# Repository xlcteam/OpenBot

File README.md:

This is a robot for the Robocup junior open competition created by Jakub Gál.
2020:
ISEF video:
https://www.youtube.com/watch?v=6aQB4FLPs9k

Robocup video:
https://vimeo.com/432606767

3D model:
https://grabcad.com/library/robocup-soccer-open-xlc-1

Dataset:
https://www.kaggle.com/jakubgal/robocup-junior-open-xlc

2021:
Video:
https://www.youtube.com/watch?v=bpfD3oBH6rc

TDP:
https://drive.google.com/drive/folders/1EIsMFVHUiWHSz9q-vNFF0SltVOlYTi-G?usp=sharing

XLC Team website:
https://xlc-team.info/

GrabCad:
https://grabcad.com/jakub.gal-2/models

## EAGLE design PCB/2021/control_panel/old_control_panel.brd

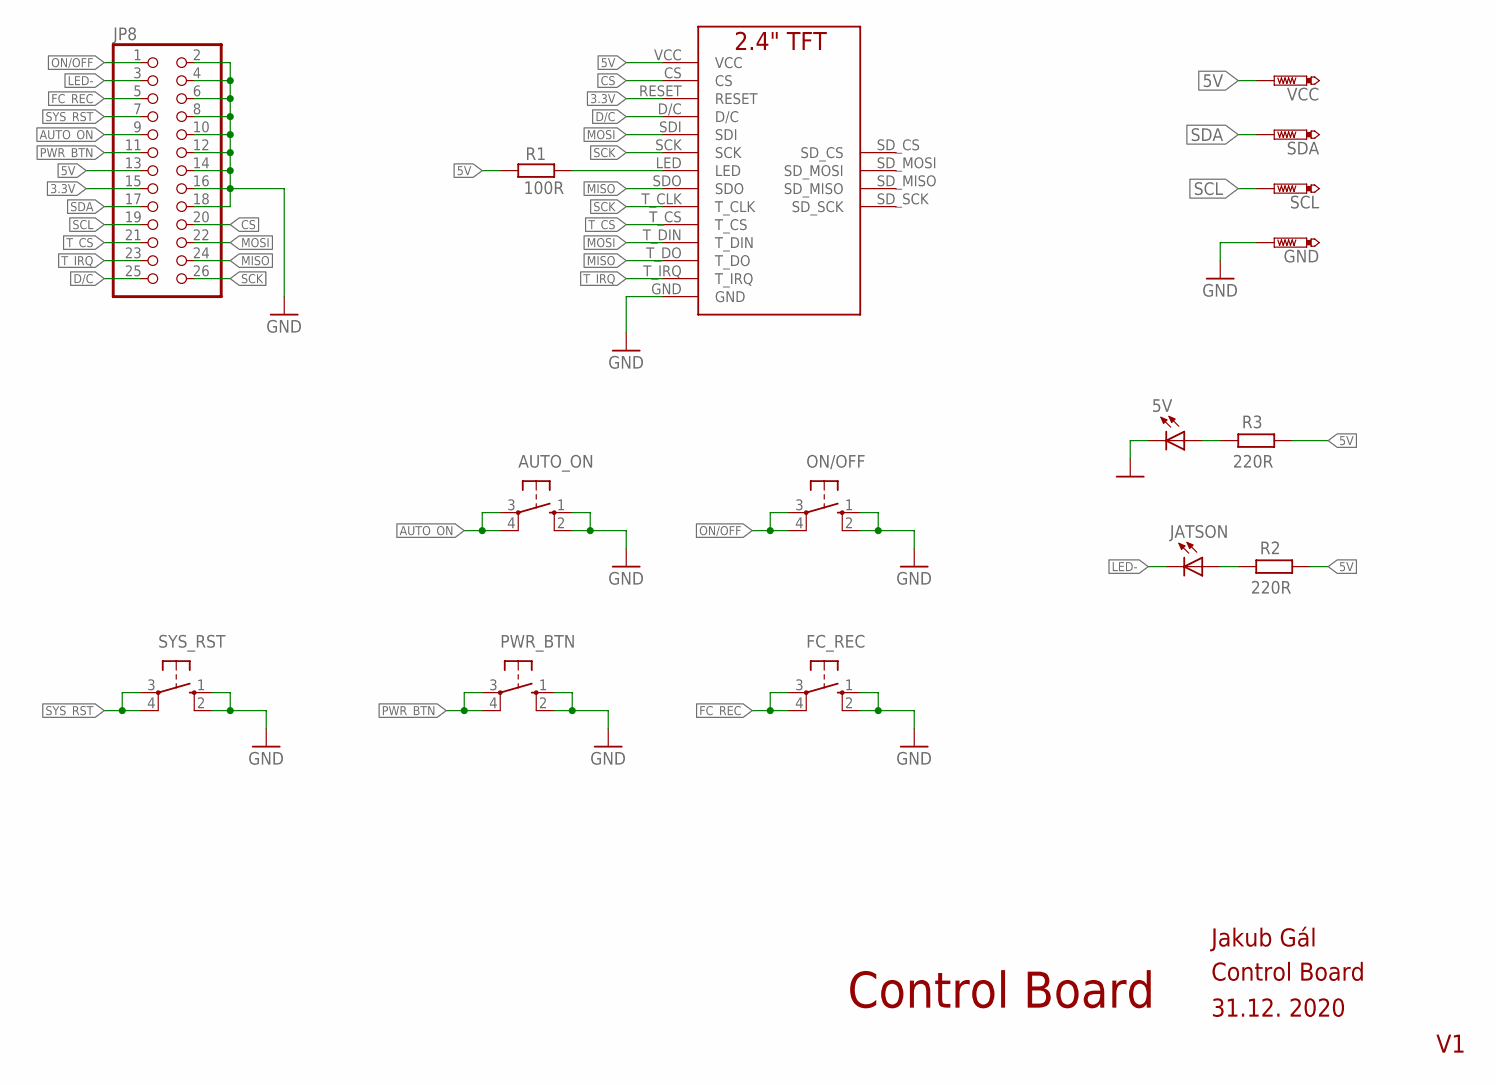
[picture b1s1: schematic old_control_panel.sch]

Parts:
5V: LEDCHIPLED_0603; CHIPLED_0603
AUTO_ON: 10-XX; B3F-10XX
FC_REC: 10-XX; B3F-10XX
GND: PTR1TP20R; TP20R
JATSON: LEDCHIPLED_0603; CHIPLED_0603
JP8: PINHD-2X13_2.54; 2X13
ON/OFF: 10-XX; B3F-10XX
PWR_BTN: 10-XX; B3F-10XX
R1: 100R; R0603
R2, R3: 220R; R0603
SCL: PTR1TP20R; TP20R
SDA: PTR1TP20R; TP20R
SYS_RST: 10-XX; B3F-10XX
U$1: 2.4"TFT; TFT_2.4"
VCC: PTR1TP20R; TP20R

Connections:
3.3V: JP8.15, U$1.RESET
5V: JP8.13, R1.1, R2.2, R3.2, U$1.VCC, VCC.TP
AUTO_ON: AUTO_ON.3, AUTO_ON.4 (P1), JP8.9
CS: JP8.20, U$1.CS
D/C: JP8.25, U$1.D/C
FC_REC: FC_REC.3, FC_REC.4 (P1), JP8.5
GND: 5V.C, AUTO_ON.1 (S), AUTO_ON.2 (S1), FC_REC.1 (S), FC_REC.2 (S1), GND.TP, JP8.2, JP8.4, JP8.6, JP8.8, JP8.10, JP8.12, JP8.14, JP8.16, JP8.18, ON/OFF.1 (S), ON/OFF.2 (S1), PWR_BTN.1 (S), PWR_BTN.2 (S1), SYS_RST.1 (S), SYS_RST.2 (S1), U$1.GND
LED-: JATSON.C, JP8.3
MISO: JP8.24, U$1.SDO, U$1.T_DO
MOSI: JP8.22, U$1.SDI, U$1.T_DIN
unnamed: R1.2, U$1.LED
unnamed: JATSON.A, R2.1
unnamed: 5V.A, R3.1
ON/OFF: JP8.1, ON/OFF.3, ON/OFF.4 (P1)
PWR_BTN: JP8.11, PWR_BTN.3, PWR_BTN.4 (P1)
SCK: JP8.26, U$1.SCK, U$1.T_CLK
SCL: JP8.19, SCL.TP
SDA: JP8.17, SDA.TP
SYS_RST: JP8.7, SYS_RST.3, SYS_RST.4 (P1)
T_CS: JP8.21, U$1.T_CS
T_IRQ: JP8.23, U$1.T_IRQ

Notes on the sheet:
Jakub Gál
Control Board
31.12. 2020

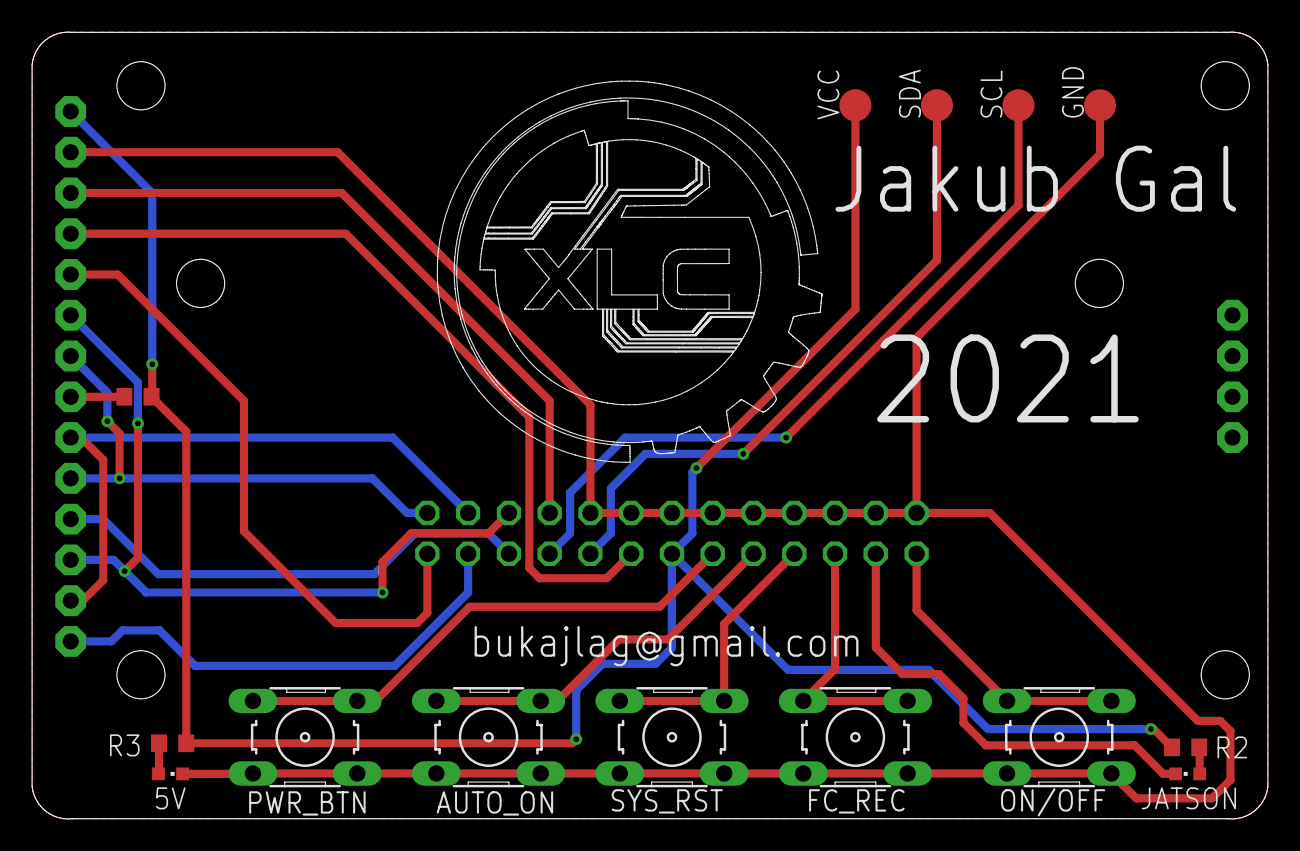
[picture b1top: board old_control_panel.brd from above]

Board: 2 copper layers, 77.0 x 49.0 mm, 16 parts (1 on the bottom side), 21 nets.

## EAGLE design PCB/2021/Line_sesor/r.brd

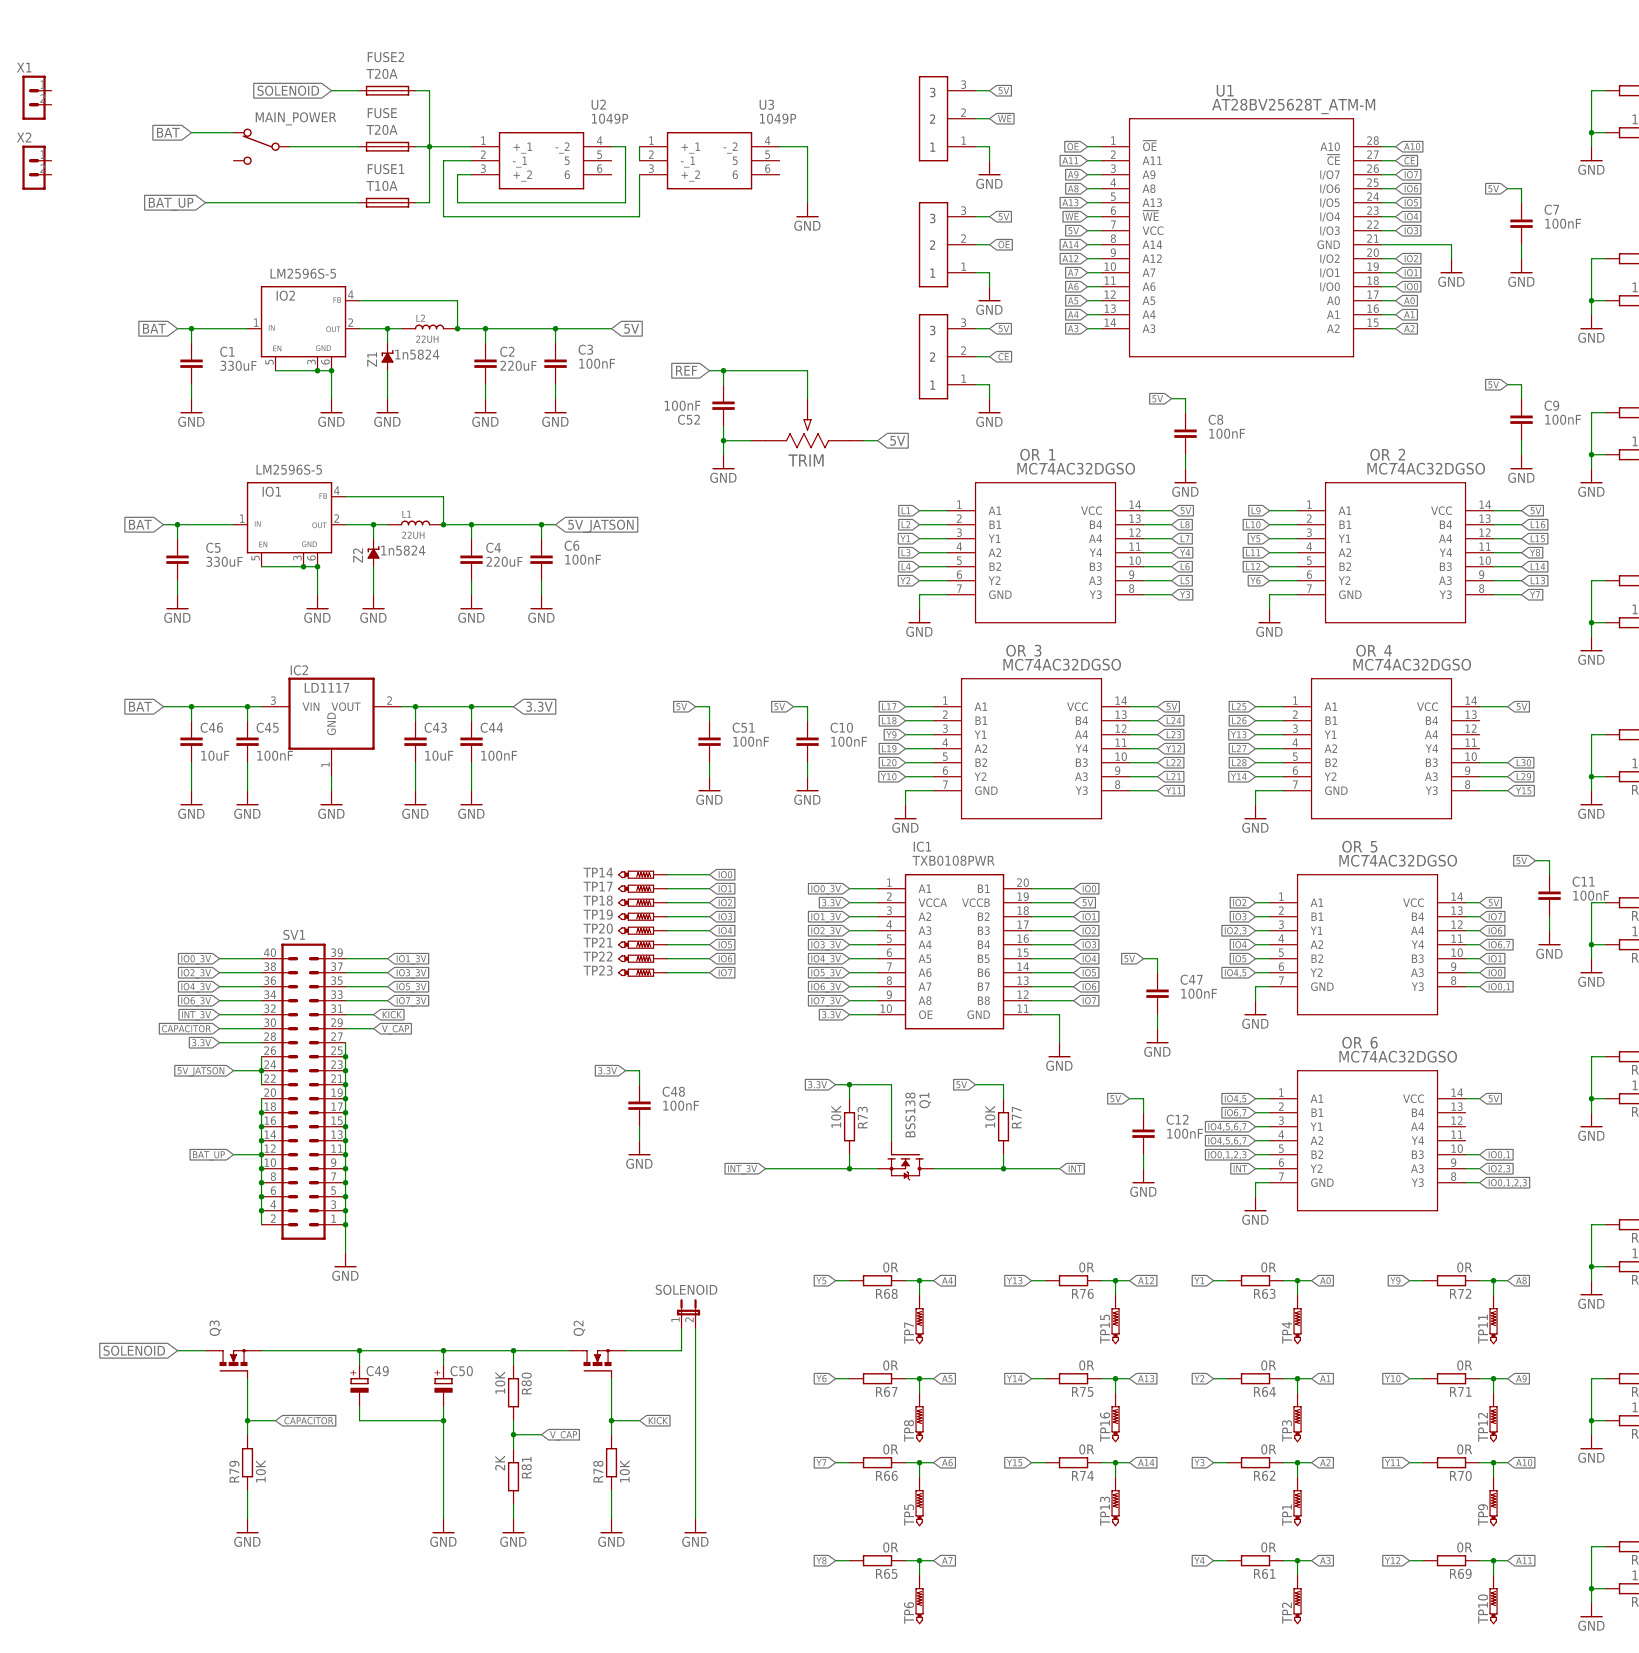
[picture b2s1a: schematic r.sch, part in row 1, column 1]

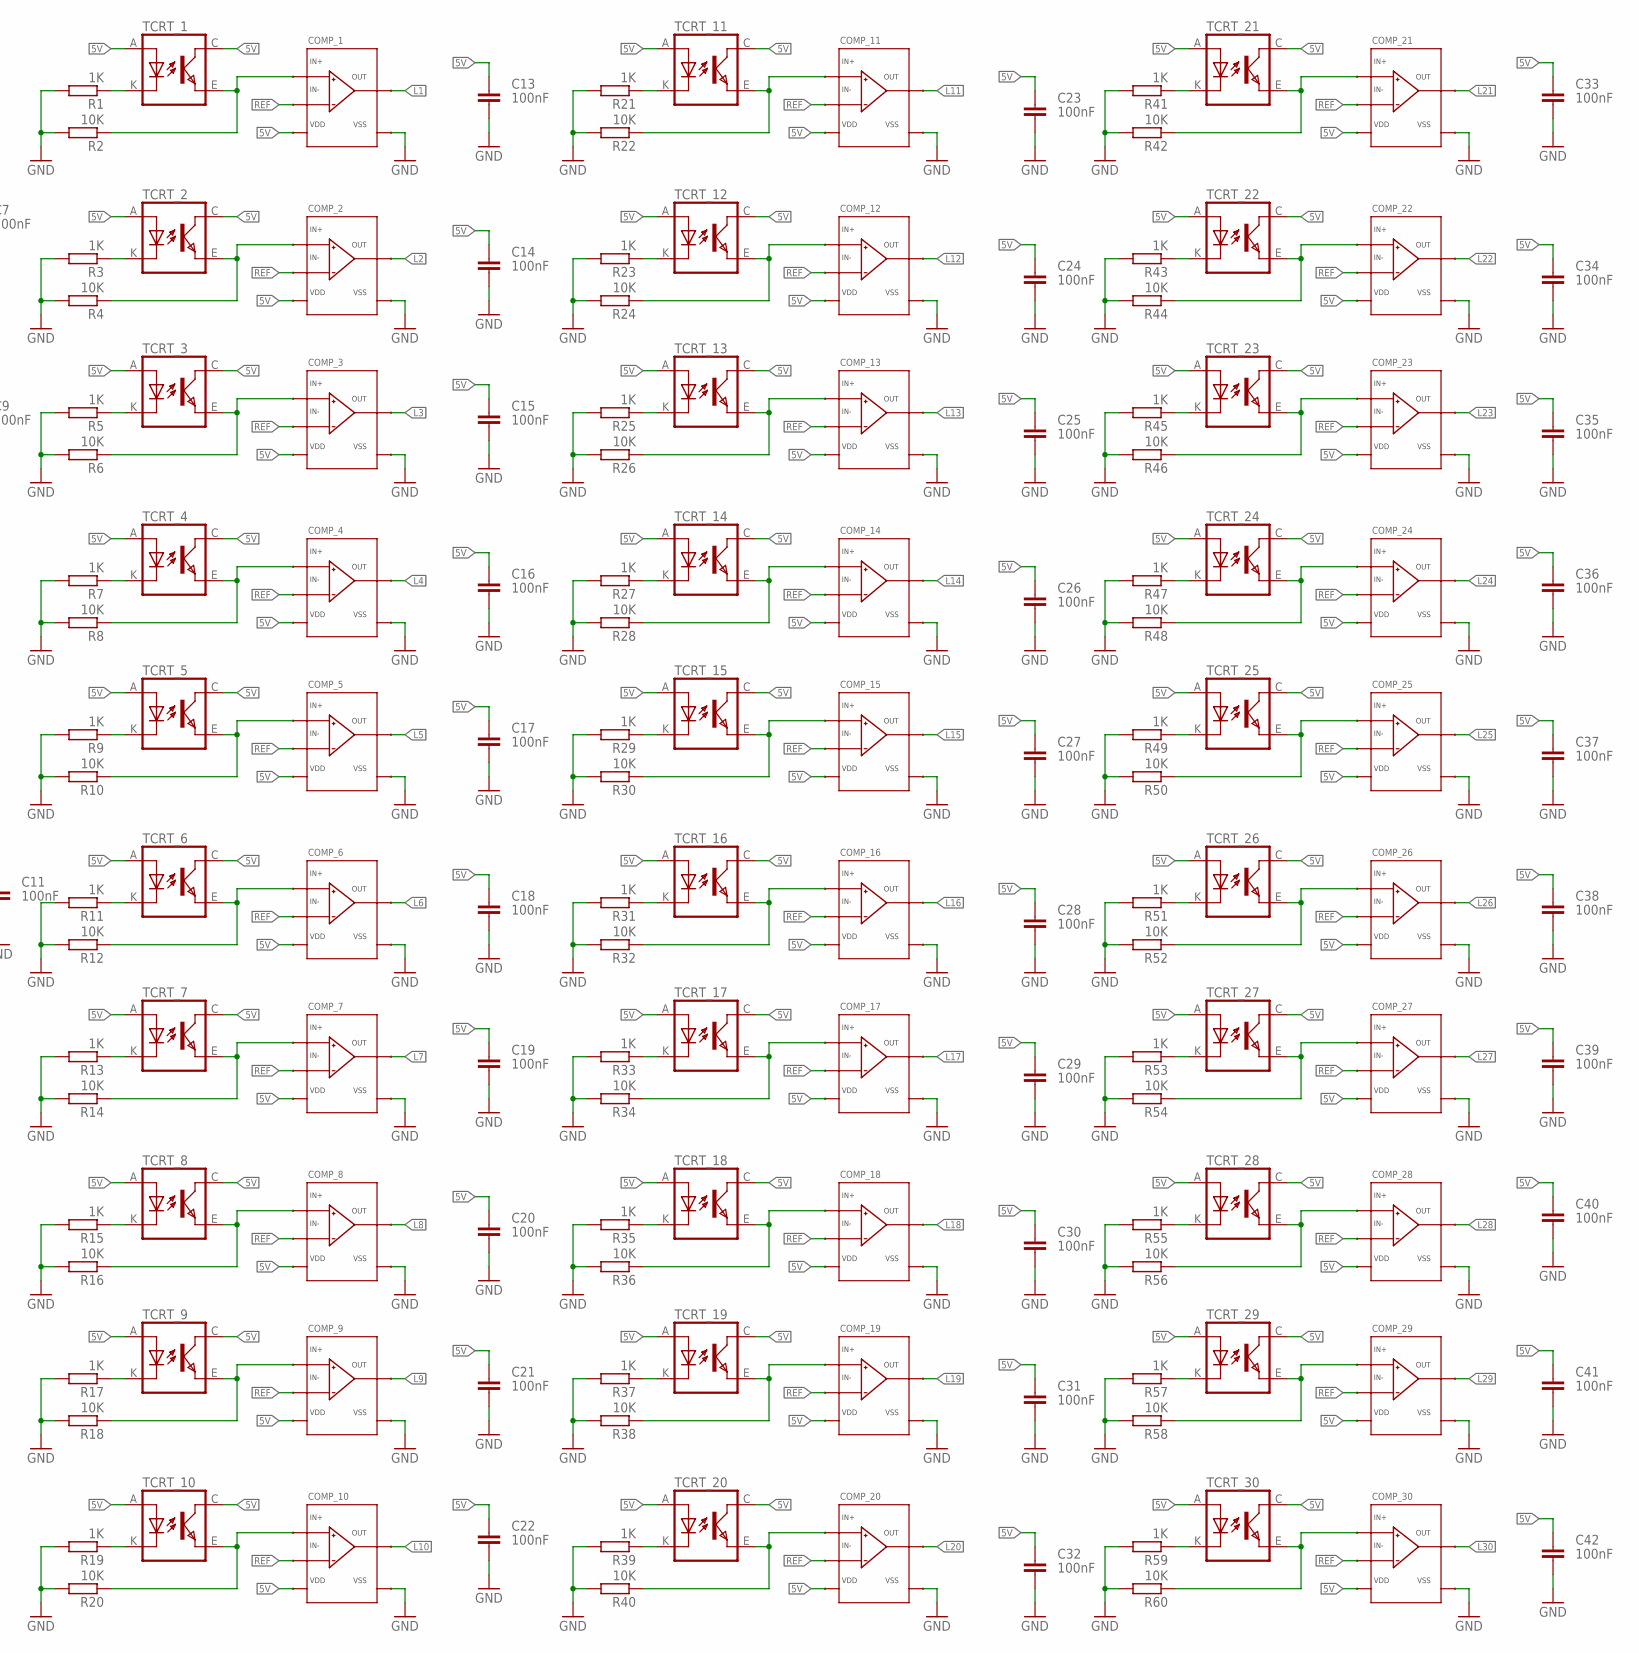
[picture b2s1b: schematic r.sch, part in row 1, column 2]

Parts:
C1, C5: 330uF; CAPM7343X310
C2, C4: 220uF; CAPM7343X310
C3, C6, C7, C8, C9, C10, C11, C12, C13, C14, C15, C16, C17, C18, C19, C20, C21, C22, C23, C24, C25, C26, C27, C28, C29, C30, C31, C32, C33, C34, C35, C36, C37, C38, C39, C40, C41, C42, C44, C45, C47, C48, C51, C52: 100nF; C0603
C43, C46: 10uF; C0603
C49, C50: CPOL-EUE10-30; EB30D
COMP_1, COMP_2, COMP_3, COMP_4, COMP_5, COMP_6, COMP_7, COMP_8, COMP_9, COMP_10, COMP_11, COMP_12, COMP_13, COMP_14, COMP_15, COMP_16, COMP_17, COMP_18, COMP_19, COMP_20, COMP_21, COMP_22, COMP_23, COMP_24, COMP_25, COMP_26, COMP_27, COMP_28, COMP_29, COMP_30: TC75S56FUTE85LF; SOT-353___(USV)_TOS
FUSE, FUSE2: T20A; SH22,5A
FUSE1: T10A; SH22,5A
IC1: TXB0108PWR; SOP65P640X120-20N
IC2: LD1117; SOT223
IO1, IO2: LM2596S-5; TO263-5
L1, L2: 22UH; INDUCTOR_L0630
MAIN_POWER: PREP-1PB; P-B069B
OR_1, OR_2, OR_3, OR_4, OR_5, OR_6: MC74AC32DGSO; SOIC-14_NB_ONS-M
Q1: BSS138; SOT23
Q2, Q3: PMOSFET_NTO220BV; TO220BV
R1, R3, R5, R7, R9, R11, R13, R15, R17, R19, R21, R23, R25, R27, R29, R31, R33, R35, R37, R39, R41, R43, R45, R47, R49, R51, R53, R55, R57, R59: 1K; R0603
R2, R4, R6, R8, R10, R12, R14, R16, R18, R20, R22, R24, R26, R28, R30, R32, R34, R36, R38, R40, R42, R44, R46, R48, R50, R52, R54, R56, R58, R60, R73, R77, R80: 10K; R0603
R61, R62, R63, R64, R65, R66, R67, R68, R69, R70, R71, R72, R74, R75, R76: 0R; R0603
R78, R79: 10K; R1206
R81: 2K; R0603
SOLENOID: JP1E; JP1
SV1: MLW40; ML40
TCRT_1, TCRT_2, TCRT_3, TCRT_4, TCRT_5, TCRT_6, TCRT_7, TCRT_8, TCRT_9, TCRT_10, TCRT_11, TCRT_12, TCRT_13, TCRT_14, TCRT_15, TCRT_16, TCRT_17, TCRT_18, TCRT_19, TCRT_20, TCRT_21, TCRT_22, TCRT_23, TCRT_24, TCRT_25, TCRT_26, TCRT_27, TCRT_28, TCRT_29, TCRT_30: TCRT5000
TP1, TP2, TP3, TP4, TP5, TP6, TP7, TP8, TP9, TP10, TP11, TP12, TP13, TP14, TP15, TP16, TP17, TP18, TP19, TP20, TP21, TP22, TP23: PTR1TP20R; TP20R
TRIM: 3362W-1-103LF; POT_3362W
U1: AT28BV25628T_ATM-M; 28T_ATM-M
U2, U3: 1049P
U$1, U$2, U$3: 0603_S
X1, X2: ML2"; ML2
Z1, Z2: 1n5824; SUPRESSOR_SMAJ

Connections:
3.3V: C43.1, C44.1, C48.1, IC1.2 (VCCA), IC1.10 (OE), IC2.2 (VOUT), Q1.1 (G), R73.1, SV1.28
5V: C2.1, C3.1, C7.1, C8.1, C9.1, C10.1, C11.1, C12.1, C13.1, C14.1, C15.1, C16.1, C17.1, C18.1, C19.1, C20.1, C21.1, C22.1, C23.1, C24.1, C25.1, C26.1, C27.1, C28.1, C29.1, C30.1, C31.1, C32.1, C33.1, C34.1, C35.1, C36.1, C37.1, C38.1, C39.1, C40.1, C41.1, C42.1, C47.1, C51.1, COMP_1.5, COMP_2.5, COMP_3.5, COMP_4.5, COMP_5.5, COMP_6.5, COMP_7.5, COMP_8.5, COMP_9.5, COMP_10.5, COMP_11.5, COMP_12.5, COMP_13.5, COMP_14.5, COMP_15.5, COMP_16.5, COMP_17.5, COMP_18.5, COMP_19.5, COMP_20.5, COMP_21.5, COMP_22.5, COMP_23.5, COMP_24.5, COMP_25.5, COMP_26.5, COMP_27.5, COMP_28.5, COMP_29.5, COMP_30.5, IC1.19 (VCCB), IO2.4 (FB), L2.2, OR_1.14 (VCC), OR_2.14 (VCC), OR_3.14 (VCC), OR_4.14 (VCC), OR_5.14 (VCC), OR_6.14 (VCC), R77.1, TCRT_1.A (ANODE), TCRT_1.C (COLLECTOR), TCRT_2.A (ANODE), TCRT_2.C (COLLECTOR), TCRT_3.A (ANODE), TCRT_3.C (COLLECTOR), TCRT_4.A (ANODE), TCRT_4.C (COLLECTOR), TCRT_5.A (ANODE), TCRT_5.C (COLLECTOR), TCRT_6.A (ANODE), TCRT_6.C (COLLECTOR), TCRT_7.A (ANODE), TCRT_7.C (COLLECTOR), TCRT_8.A (ANODE), TCRT_8.C (COLLECTOR), TCRT_9.A (ANODE), TCRT_9.C (COLLECTOR), TCRT_10.A (ANODE), TCRT_10.C (COLLECTOR), TCRT_11.A (ANODE), TCRT_11.C (COLLECTOR), TCRT_12.A (ANODE), TCRT_12.C (COLLECTOR), TCRT_13.A (ANODE), TCRT_13.C (COLLECTOR), TCRT_14.A (ANODE), TCRT_14.C (COLLECTOR), TCRT_15.A (ANODE), TCRT_15.C (COLLECTOR), TCRT_16.A (ANODE), TCRT_16.C (COLLECTOR), TCRT_17.A (ANODE), TCRT_17.C (COLLECTOR), TCRT_18.A (ANODE), TCRT_18.C (COLLECTOR), TCRT_19.A (ANODE), TCRT_19.C (COLLECTOR), TCRT_20.A (ANODE), TCRT_20.C (COLLECTOR), TCRT_21.A (ANODE), TCRT_21.C (COLLECTOR), TCRT_22.A (ANODE), TCRT_22.C (COLLECTOR), TCRT_23.A (ANODE), TCRT_23.C (COLLECTOR), TCRT_24.A (ANODE), TCRT_24.C (COLLECTOR), TCRT_25.A (ANODE), TCRT_25.C (COLLECTOR), TCRT_26.A (ANODE), TCRT_26.C (COLLECTOR), TCRT_27.A (ANODE), TCRT_27.C (COLLECTOR), TCRT_28.A (ANODE), TCRT_28.C (COLLECTOR), TCRT_29.A (ANODE), TCRT_29.C (COLLECTOR), TCRT_30.A (ANODE)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
5V_JATSON: C4.1, C6.1, IO1.4 (FB), L1.2, SV1.22, SV1.24, SV1.26
!CE: U1.27 (!CE), U$3.2 (A2)
!OE: U1.1 (!OE), U$2.2 (A2)
!WE: U1.6 (!WE), U$1.2 (A2)
A0: R63.1, TP4.TP, U1.17 (A0)
A1: R64.1, TP3.TP, U1.16 (A1)
A2: R62.1, TP1.TP, U1.15 (A2)
A3: R61.1, TP2.TP, U1.14 (A3)
A4: R68.1, TP7.TP, U1.13 (A4)
A5: R67.1, TP8.TP, U1.12 (A5)
A6: R66.1, TP5.TP, U1.11 (A6)
A7: R65.1, TP6.TP, U1.10 (A7)
A8: R72.1, TP11.TP, U1.4 (A8)
A9: R71.1, TP12.TP, U1.3 (A9)
A10: R70.1, TP9.TP, U1.28 (A10)
A11: R69.1, TP10.TP, U1.2 (A11)
A12: R76.1, TP15.TP, U1.9 (A12)
A13: R75.1, TP16.TP, U1.5 (A13)
A14: R74.1, TP13.TP, U1.8 (A14)
BAT: C1.1, C5.1, C45.1, C46.1, IC2.3 (VIN), IO1.1 (IN), IO2.1 (IN), MAIN_POWER.3 (3-ON)
BAT_UP: FUSE1.1, SV1.2, SV1.4, SV1.6, SV1.8, SV1.10, SV1.12, SV1.14, SV1.16, SV1.18, SV1.20
CAPACITOR: Q3.G, R79.2, SV1.30
GND: C1.2, C2.2, C3.2, C4.2, C5.2, C6.2, C7.2, C8.2, C9.2, C10.2, C11.2, C12.2, C13.2, C14.2, C15.2, C16.2, C17.2, C18.2, C19.2, C20.2, C21.2, C22.2, C23.2, C24.2, C25.2, C26.2, C27.2, C28.2, C29.2, C30.2, C31.2, C32.2, C33.2, C34.2, C35.2, C36.2, C37.2, C38.2, C39.2, C40.2, C41.2, C42.2, C43.2, C44.2, C45.2, C46.2, C47.2, C48.2, C49.-, C50.-, C51.2, C52.1, COMP_1.2, COMP_2.2, COMP_3.2, COMP_4.2, COMP_5.2, COMP_6.2, COMP_7.2, COMP_8.2, COMP_9.2, COMP_10.2, COMP_11.2, COMP_12.2, COMP_13.2, COMP_14.2, COMP_15.2, COMP_16.2, COMP_17.2, COMP_18.2, COMP_19.2, COMP_20.2, COMP_21.2, COMP_22.2, COMP_23.2, COMP_24.2, COMP_25.2, COMP_26.2, COMP_27.2, COMP_28.2, COMP_29.2, COMP_30.2, IC1.11 (GND), IC2.1 (GND), IO1.3 (GND), IO1.5 (EN), IO1.6 (GND), IO2.3 (GND), IO2.5 (EN), IO2.6 (GND), OR_1.7 (GND), OR_2.7 (GND), OR_3.7 (GND), OR_4.7 (GND), OR_5.7 (GND), OR_6.7 (GND), R1.2, R2.2, R3.2, R4.2, R5.2, R6.2, R7.2, R8.2, R9.2, R10.2, R11.2, R12.2, R13.2, R14.2, R15.2, R16.2, R17.2, R18.2, R19.2, R20.2, R21.2, R22.2, R23.2, R24.2, R25.2, R26.2, R27.2, R28.2, R29.2, R30.2, R31.2, R32.2, R33.2, R34.2, R35.2, R36.2, R37.2, R38.2, R39.2, R40.2, R41.2, R42.2, R43.2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
INT: OR_6.6 (Y2), Q1.3 (D), R77.2
INT_3V: Q1.2 (S), R73.2, SV1.32
IO0: IC1.20 (B1), OR_5.9 (A3), TP14.TP, U1.18 (I/O0)
IO0,1: OR_5.8 (Y3), OR_6.10 (B3)
IO0,1,2,3: OR_6.5 (B2), OR_6.8 (Y3)
IO0_3V: IC1.1 (A1), SV1.40
IO1: IC1.18 (B2), OR_5.10 (B3), TP17.TP, U1.19 (I/O1)
IO1_3V: IC1.3 (A2), SV1.39
IO2: IC1.17 (B3), OR_5.1 (A1), TP18.TP, U1.20 (I/O2)
IO2,3: OR_5.3 (Y1), OR_6.9 (A3)
IO2_3V: IC1.4 (A3), SV1.38
IO3: IC1.16 (B4), OR_5.2 (B1), TP19.TP, U1.22 (I/O3)
IO3_3V: IC1.5 (A4), SV1.37
IO4: IC1.15 (B5), OR_5.4 (A2), TP20.TP, U1.23 (I/O4)
IO4,5: OR_5.6 (Y2), OR_6.1 (A1)
IO4,5,6,7: OR_6.3 (Y1), OR_6.4 (A2)
IO4_3V: IC1.6 (A5), SV1.36
IO5: IC1.14 (B6), OR_5.5 (B2), TP21.TP, U1.24 (I/O5)
IO5_3V: IC1.7 (A6), SV1.35
IO6: IC1.13 (B7), OR_5.12 (A4), TP22.TP, U1.25 (I/O6)
IO6,7: OR_5.11 (Y4), OR_6.2 (B1)
IO6_3V: IC1.8 (A7), SV1.34
IO7: IC1.12 (B8), OR_5.13 (B4), TP23.TP, U1.26 (I/O7)
IO7_3V: IC1.9 (A8), SV1.33
KICK: Q2.G, R78.2, SV1.31
L1: COMP_1.4, OR_1.1 (A1)
L2: COMP_2.4, OR_1.2 (B1)
L3: COMP_3.4, OR_1.4 (A2)
L4: COMP_4.4, OR_1.5 (B2)
L5: COMP_5.4, OR_1.9 (A3)
L6: COMP_6.4, OR_1.10 (B3)
L7: COMP_7.4, OR_1.12 (A4)
L8: COMP_8.4, OR_1.13 (B4)
L9: COMP_9.4, OR_2.1 (A1)
L10: COMP_10.4, OR_2.2 (B1)
L11: COMP_11.4, OR_2.4 (A2)
L12: COMP_12.4, OR_2.5 (B2)
L13: COMP_13.4, OR_2.9 (A3)
L14: COMP_14.4, OR_2.10 (B3)
L15: COMP_15.4, OR_2.12 (A4)
L16: COMP_16.4, OR_2.13 (B4)
L17: COMP_17.4, OR_3.1 (A1)
L18: COMP_18.4, OR_3.2 (B1)
L19: COMP_19.4, OR_3.4 (A2)
L20: COMP_20.4, OR_3.5 (B2)
L21: COMP_21.4, OR_3.9 (A3)
L22: COMP_22.4, OR_3.10 (B3)
L23: COMP_23.4, OR_3.12 (A4)
L24: COMP_24.4, OR_3.13 (B4)
L25: COMP_25.4, OR_4.1 (A1)
L26: COMP_26.4, OR_4.2 (B1)
L27: COMP_27.4, OR_4.4 (A2)
L28: COMP_28.4, OR_4.5 (B2)
L29: COMP_29.4, OR_4.9 (A3)
L30: COMP_30.4, OR_4.10 (B3)
unnamed: R1.1, TCRT_1.K (CATHODE)
unnamed: COMP_1.3, R2.1, TCRT_1.E (EMITTER)
unnamed: R3.1, TCRT_2.K (CATHODE)
unnamed: COMP_2.3, R4.1, TCRT_2.E (EMITTER)
unnamed: R5.1, TCRT_3.K (CATHODE)
unnamed: COMP_3.3, R6.1, TCRT_3.E (EMITTER)
unnamed: R7.1, TCRT_4.K (CATHODE)
unnamed: COMP_4.3, R8.1, TCRT_4.E (EMITTER)
unnamed: R9.1, TCRT_5.K (CATHODE)
unnamed: COMP_5.3, R10.1, TCRT_5.E (EMITTER)
unnamed: R11.1, TCRT_6.K (CATHODE)
unnamed: COMP_6.3, R12.1, TCRT_6.E (EMITTER)
unnamed: R13.1, TCRT_7.K (CATHODE)
unnamed: COMP_7.3, R14.1, TCRT_7.E (EMITTER)
unnamed: R15.1, TCRT_8.K (CATHODE)
unnamed: COMP_8.3, R16.1, TCRT_8.E (EMITTER)
unnamed: R17.1, TCRT_9.K (CATHODE)
unnamed: COMP_9.3, R18.1, TCRT_9.E (EMITTER)
unnamed: R19.1, TCRT_10.K (CATHODE)
unnamed: COMP_10.3, R20.1, TCRT_10.E (EMITTER)
unnamed: R21.1, TCRT_11.K (CATHODE)
unnamed: COMP_11.3, R22.1, TCRT_11.E (EMITTER)
unnamed: R23.1, TCRT_12.K (CATHODE)
unnamed: COMP_12.3, R24.1, TCRT_12.E (EMITTER)
unnamed: R25.1, TCRT_13.K (CATHODE)
unnamed: COMP_13.3, R26.1, TCRT_13.E (EMITTER)
unnamed: R27.1, TCRT_14.K (CATHODE)
unnamed: COMP_14.3, R28.1, TCRT_14.E (EMITTER)
unnamed: R29.1, TCRT_15.K (CATHODE)
unnamed: COMP_15.3, R30.1, TCRT_15.E (EMITTER)
unnamed: R31.1, TCRT_16.K (CATHODE)
unnamed: COMP_16.3, R32.1, TCRT_16.E (EMITTER)
unnamed: R33.1, TCRT_17.K (CATHODE)
unnamed: COMP_17.3, R34.1, TCRT_17.E (EMITTER)
unnamed: R35.1, TCRT_18.K (CATHODE)
unnamed: COMP_18.3, R36.1, TCRT_18.E (EMITTER)
unnamed: R37.1, TCRT_19.K (CATHODE)
unnamed: COMP_19.3, R38.1, TCRT_19.E (EMITTER)
unnamed: R39.1, TCRT_20.K (CATHODE)
unnamed: COMP_20.3, R40.1, TCRT_20.E (EMITTER)
unnamed: R41.1, TCRT_21.K (CATHODE)
unnamed: COMP_21.3, R42.1, TCRT_21.E (EMITTER)
unnamed: R43.1, TCRT_22.K (CATHODE)
unnamed: COMP_22.3, R44.1, TCRT_22.E (EMITTER)
unnamed: R45.1, TCRT_23.K (CATHODE)
unnamed: COMP_23.3, R46.1, TCRT_23.E (EMITTER)
unnamed: R47.1, TCRT_24.K (CATHODE)
unnamed: COMP_24.3, R48.1, TCRT_24.E (EMITTER)
unnamed: R49.1, TCRT_25.K (CATHODE)
unnamed: COMP_25.3, R50.1, TCRT_25.E (EMITTER)
unnamed: R51.1, TCRT_26.K (CATHODE)
unnamed: COMP_26.3, R52.1, TCRT_26.E (EMITTER)
unnamed: R53.1, TCRT_27.K (CATHODE)
unnamed: COMP_27.3, R54.1, TCRT_27.E (EMITTER)
unnamed: R55.1, TCRT_28.K (CATHODE)
unnamed: COMP_28.3, R56.1, TCRT_28.E (EMITTER)
unnamed: R57.1, TCRT_29.K (CATHODE)
unnamed: COMP_29.3, R58.1, TCRT_29.E (EMITTER)
unnamed: R59.1, TCRT_30.K (CATHODE)
unnamed: COMP_30.3, R60.1, TCRT_30.E (EMITTER)
unnamed: IO2.2 (OUT), L2.1, Z1.C
unnamed: IO1.2 (OUT), L1.1, Z2.C
unnamed: U2.3 (+_2), U2.4 (-_2)
unnamed: U3.1 (+_1), U3.2 (-_1)
unnamed: U2.2 (-_1), U3.3 (+_2)
unnamed: FUSE.2, FUSE1.2, FUSE2.2, U2.1 (+_1)
unnamed: FUSE.1, MAIN_POWER.2 (2-COM)
unnamed: C49.+, C50.+, Q2.D, Q3.S, R80.1
unnamed: Q2.S, SOLENOID.1
REF: C52.2, COMP_1.1, COMP_2.1, COMP_3.1, COMP_4.1, COMP_5.1, COMP_6.1, COMP_7.1, COMP_8.1, COMP_9.1, COMP_10.1, COMP_11.1, COMP_12.1, COMP_13.1, COMP_14.1, COMP_15.1, COMP_16.1, COMP_17.1, COMP_18.1, COMP_19.1, COMP_20.1, COMP_21.1, COMP_22.1, COMP_23.1, COMP_24.1, COMP_25.1, COMP_26.1, COMP_27.1, COMP_28.1, COMP_29.1, COMP_30.1, TRIM.2
SOLENOID: FUSE2.1, Q3.D
V_CAP: R80.2, R81.1, SV1.29
Y1: OR_1.3 (Y1), R63.2
Y2: OR_1.6 (Y2), R64.2
Y3: OR_1.8 (Y3), R62.2
Y4: OR_1.11 (Y4), R61.2
Y5: OR_2.3 (Y1), R68.2
Y6: OR_2.6 (Y2), R67.2
Y7: OR_2.8 (Y3), R66.2
Y8: OR_2.11 (Y4), R65.2
Y9: OR_3.3 (Y1), R72.2
Y10: OR_3.6 (Y2), R71.2
Y11: OR_3.8 (Y3), R70.2
Y12: OR_3.11 (Y4), R69.2
Y13: OR_4.3 (Y1), R76.2
Y14: OR_4.6 (Y2), R75.2
Y15: OR_4.8 (Y3), R74.2

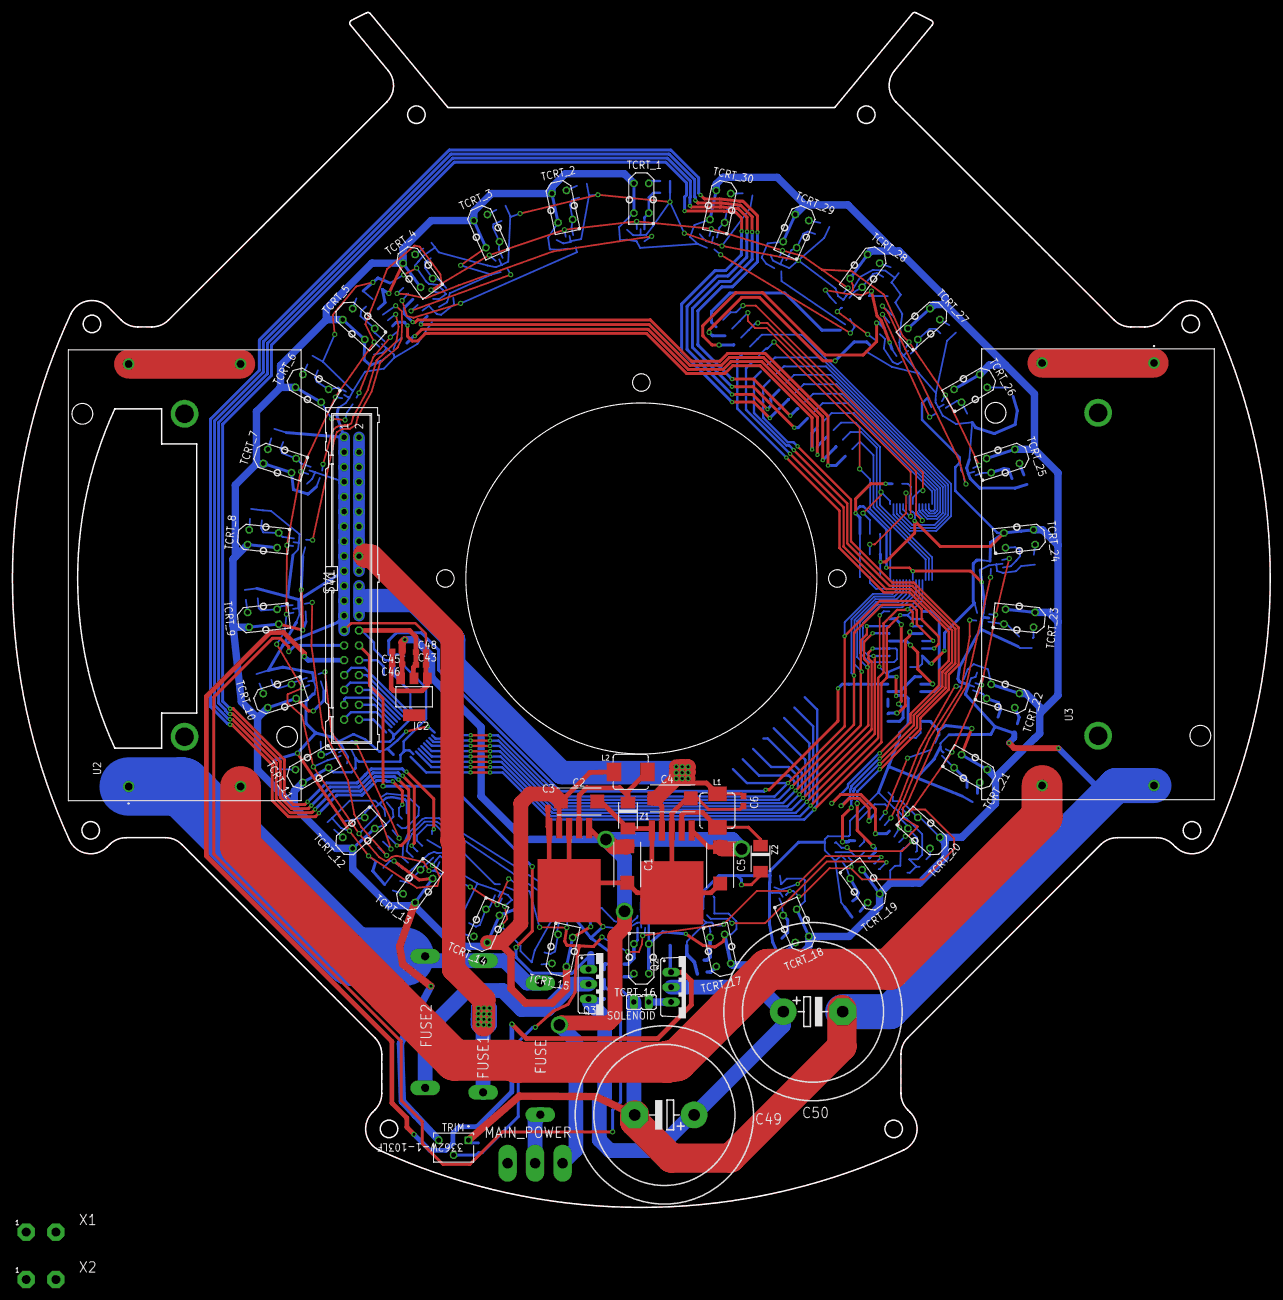
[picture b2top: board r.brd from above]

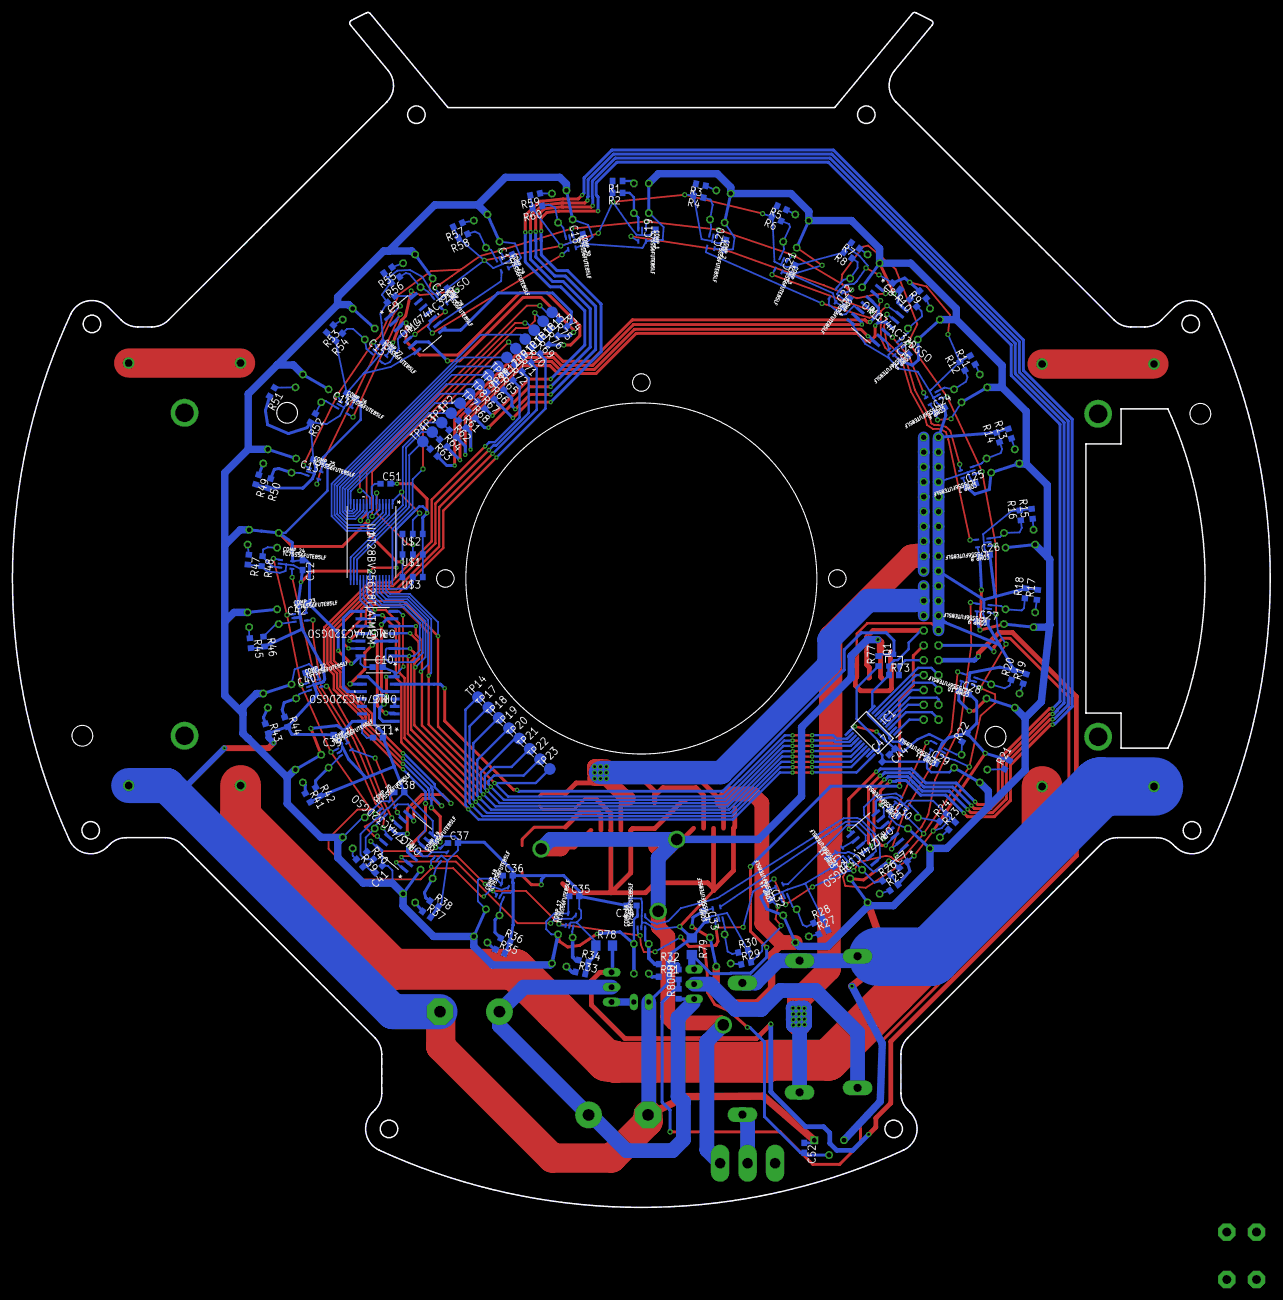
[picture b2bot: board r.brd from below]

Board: 2 copper layers, 215.0 x 204.3 mm, 248 parts (186 on the bottom side), 167 nets.

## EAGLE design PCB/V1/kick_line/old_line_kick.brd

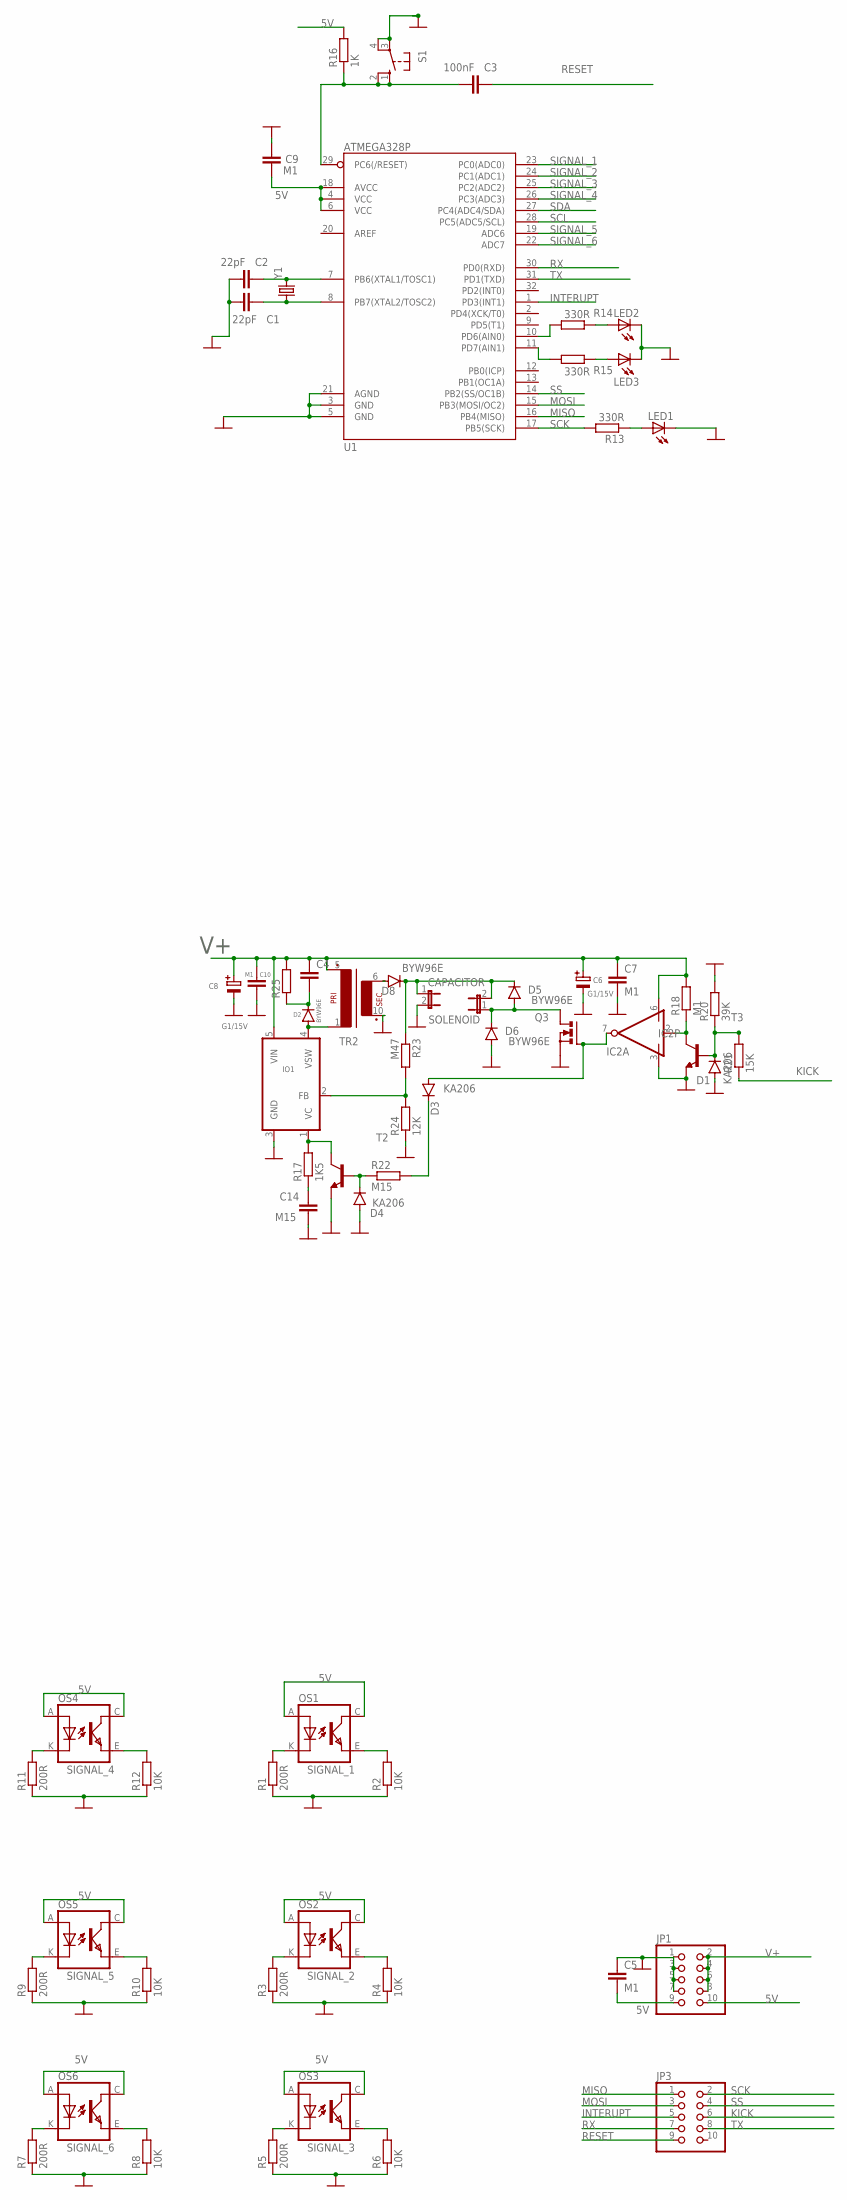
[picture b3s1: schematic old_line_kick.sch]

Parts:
C1, C2: 22pF; C0603
C3: 100nF; C0603
C4: C-EU075-052X106; C075-052X106
C5, C9: M1; C0603
C6, C8: G1/15V; E-2,5/7-RAD
C7, C10: M1; C0805K
C14: M15; C1206
CAPACITOR: JP1E; JP1
D1, D3, D4: KA206; D-7.5
D2, D5, D6, D8: BYW96E; SOD64-10
IC2: MIC4423BM; SO08
IO1: LT1071V; TO220-5P
JP1, JP3: PINHD-2X5IDC; 2X05_IDC
LED1, LED2, LED3: LEDCHIPLED_0603; CHIPLED_0603
OS1, OS2, OS3, OS4, OS5, OS6: TCRT5000
Q3: PMOSFET_NTO220BV; TO220BV
R1, R3, R5, R7, R9, R11: 200R; R0603
R2, R4, R6, R8, R10, R12: 10K; R0603
R13, R14, R15: 330R; R0603
R16: 1K; R0603
R17: 1K5; R1206
R18: M1; R1206
R20: 39K; R1206
R21: 15K; R1206
R22: M15; R1206
R23: M47; R1206
R24: 12K; R1206
R25: REZISTOR-7,5MM-HORIZ; R-7,5H
S1: 10-XX; B3F-10XX
SOLENOID: JP1E; JP1
T2, T3: -NPN-SC59-BEC; SC59-BEC
TR2: TRAFO-E10-R""; TRAFO-EE17X20
U1: ATMEGA328P; TQFP32-08
Y1: CRYSTALHC49US; HC49US

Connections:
5V: C5.2, C9.1, JP1.9, JP1.10, OS1.A (ANODE), OS1.C (COLLECTOR), OS2.A (ANODE), OS2.C (COLLECTOR), OS3.A (ANODE), OS3.C (COLLECTOR), OS4.A (ANODE), OS4.C (COLLECTOR), OS5.A (ANODE), OS5.C (COLLECTOR), OS6.A (ANODE), OS6.C (COLLECTOR), R16.2, U1.4 (VCC), U1.6 (VCC), U1.18 (AVCC)
GND: C1.1, C2.1, C5.1, C6.-, C7.2, C8.-, C9.2, C10.2, C14.2, CAPACITOR.2, D1.A, D4.A, D6.A, IC2.3 (GND), IO1.3 (GND), JP1.1, JP1.3, JP1.5, JP1.7, LED1.C, LED2.C, LED3.C, Q3.S, R1.1, R2.1, R3.1, R4.1, R5.1, R6.1, R7.1, R8.1, R9.1, R10.1, R11.1, R12.1, R20.2, R24.1, S1.3, S1.4 (P1), T2.E, T3.E, TR2.10 (4), U1.3 (GND), U1.5 (GND), U1.21 (AGND)
INTERUPT: JP3.5, U1.1 (PD3(INT1))
KICK: JP3.6, R21.1
MISO: JP3.1, U1.16 (PB4(MISO))
MOSI: JP3.3, U1.15 (PB3(MOSI/OC2))
unnamed: OS1.K (CATHODE), R1.2
unnamed: OS2.K (CATHODE), R3.2
unnamed: OS3.K (CATHODE), R5.2
unnamed: OS6.K (CATHODE), R7.2
unnamed: OS5.K (CATHODE), R9.2
unnamed: OS4.K (CATHODE), R11.2
unnamed: C2.2, U1.7 (PB6(XTAL1/TOSC1)), Y1.2
unnamed: C1.2, U1.8 (PB7(XTAL2/TOSC2)), Y1.1
unnamed: IO1.1 (VC), R17.2, T2.C
unnamed: C14.1, R17.1
unnamed: D8.A, TR2.6 (3)
unnamed: D3.A, IC2.7 (OUT), Q3.G
unnamed: CAPACITOR.1, D5.C, D8.C, R23.1, SOLENOID.2
unnamed: IO1.2 (FB), R23.2, R24.2
unnamed: D4.C, R22.1, T2.B
unnamed: C3.1, R16.1, S1.1 (S), S1.2 (S1), U1.29 (PC6(/RESET))
unnamed: LED1.A, R13.1
unnamed: IC2.2 (IN), R18.1, T3.C
unnamed: LED2.A, R14.1
unnamed: R15.2, U1.11 (PD7(AIN1))
unnamed: LED3.A, R15.1
unnamed: R14.2, U1.10 (PD6(AIN0))
unnamed: D2.A, IO1.4 (VSW), TR2.1
unnamed: C4.2, D2.C, R25.1
unnamed: D5.A, D6.C, Q3.D, SOLENOID.1
unnamed: D3.C, R22.2
unnamed: D1.C, R20.1, R21.2, T3.B
RESET: C3.2, JP3.9
RX: JP3.7, U1.30 (PD0(RXD))
SCK: JP3.2, R13.2, U1.17 (PB5(SCK))
SCL: U1.28 (PC5(ADC5/SCL))
SDA: U1.27 (PC4(ADC4/SDA))
SIGNAL_1: OS1.E (EMITTER), R2.2, U1.23 (PC0(ADC0))
SIGNAL_2: OS2.E (EMITTER), R4.2, U1.24 (PC1(ADC1))
SIGNAL_3: OS3.E (EMITTER), R6.2, U1.25 (PC2(ADC2))
SIGNAL_4: OS4.E (EMITTER), R12.2, U1.26 (PC3(ADC3))
SIGNAL_5: OS5.E (EMITTER), R10.2, U1.19 (ADC6)
SIGNAL_6: OS6.E (EMITTER), R8.2, U1.22 (ADC7)
SS: JP3.4, U1.14 (PB2(SS/OC1B))
TX: JP3.8, U1.31 (PD1(TXD))
V+: C4.1, C6.+, C7.1, C8.+, C10.1, IC2.6 (V+), IO1.5 (VIN), JP1.2, JP1.4, JP1.6, JP1.8, R18.2, R25.2, TR2.5 (2)

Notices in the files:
parts and their libraries:
COPYRIGHT: Copyright (C) 2016 Accelerated Designs. All rights reserved
SparkFun-DigitalIC: Licensing: CC v3.0 Share-Alike You are welcome to use this library for commercial purposes.
